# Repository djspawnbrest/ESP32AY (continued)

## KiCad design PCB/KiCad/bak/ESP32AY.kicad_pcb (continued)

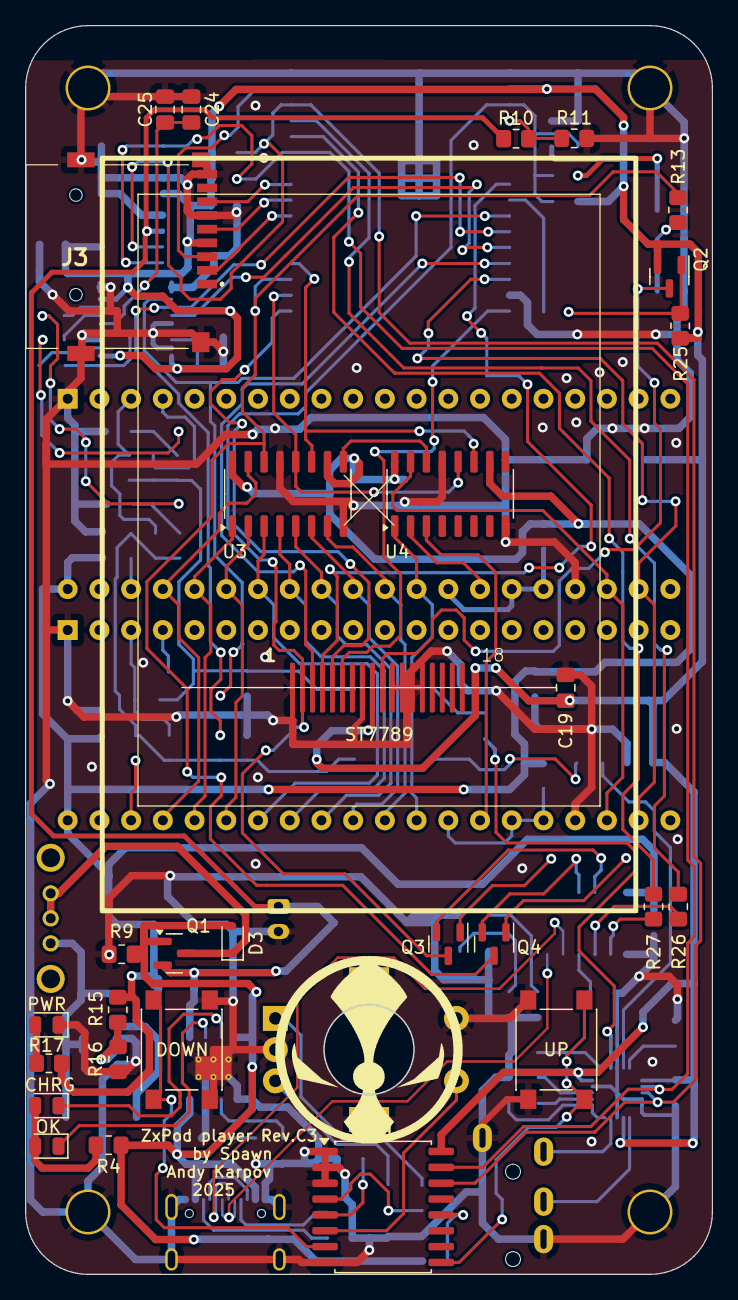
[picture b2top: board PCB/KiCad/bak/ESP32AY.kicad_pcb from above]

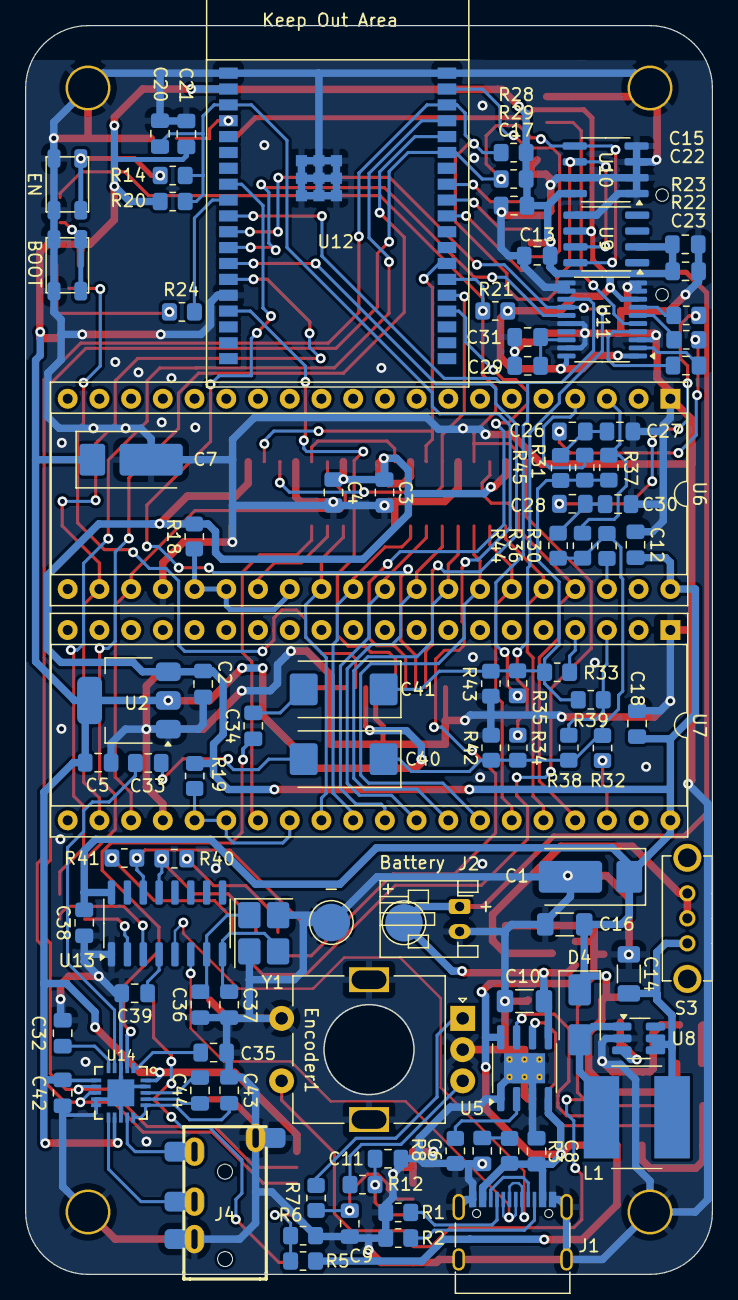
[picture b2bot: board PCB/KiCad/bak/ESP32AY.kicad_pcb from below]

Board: 2 copper layers, 55.0 x 100.0 mm, 127 parts (97 on the bottom side), 106 nets.

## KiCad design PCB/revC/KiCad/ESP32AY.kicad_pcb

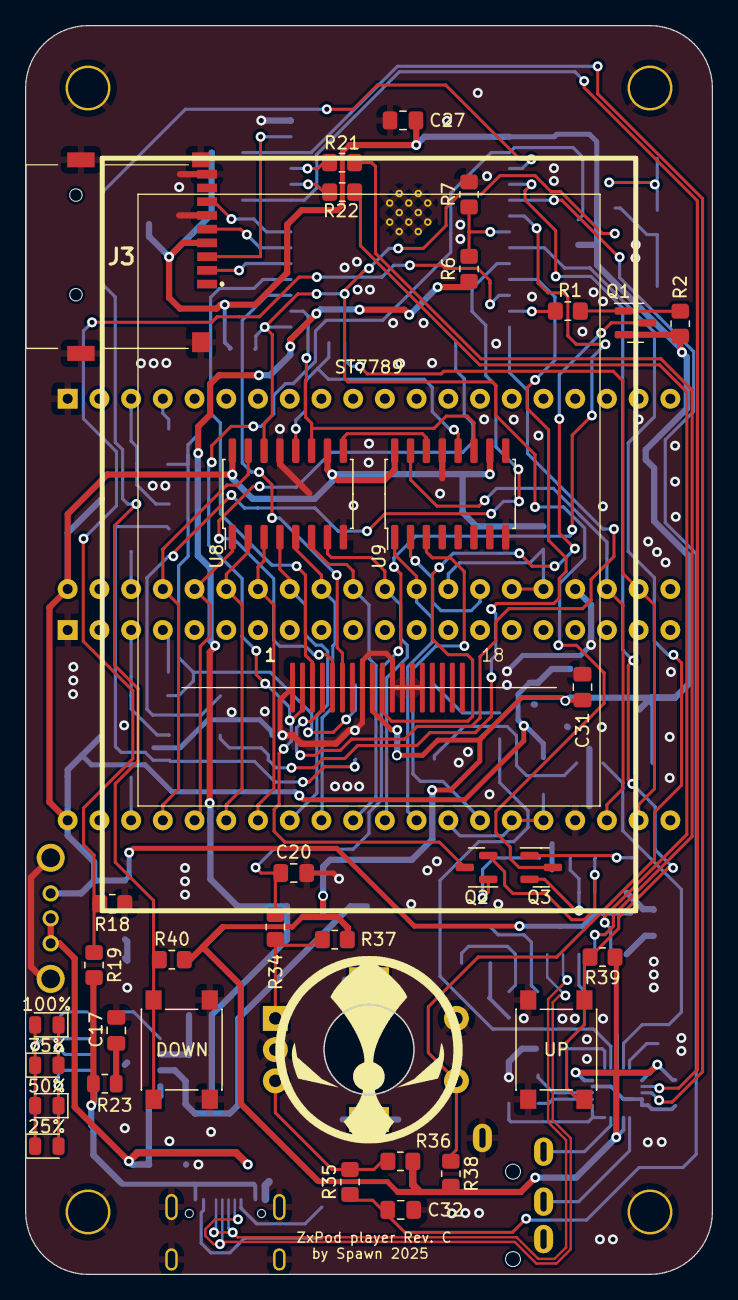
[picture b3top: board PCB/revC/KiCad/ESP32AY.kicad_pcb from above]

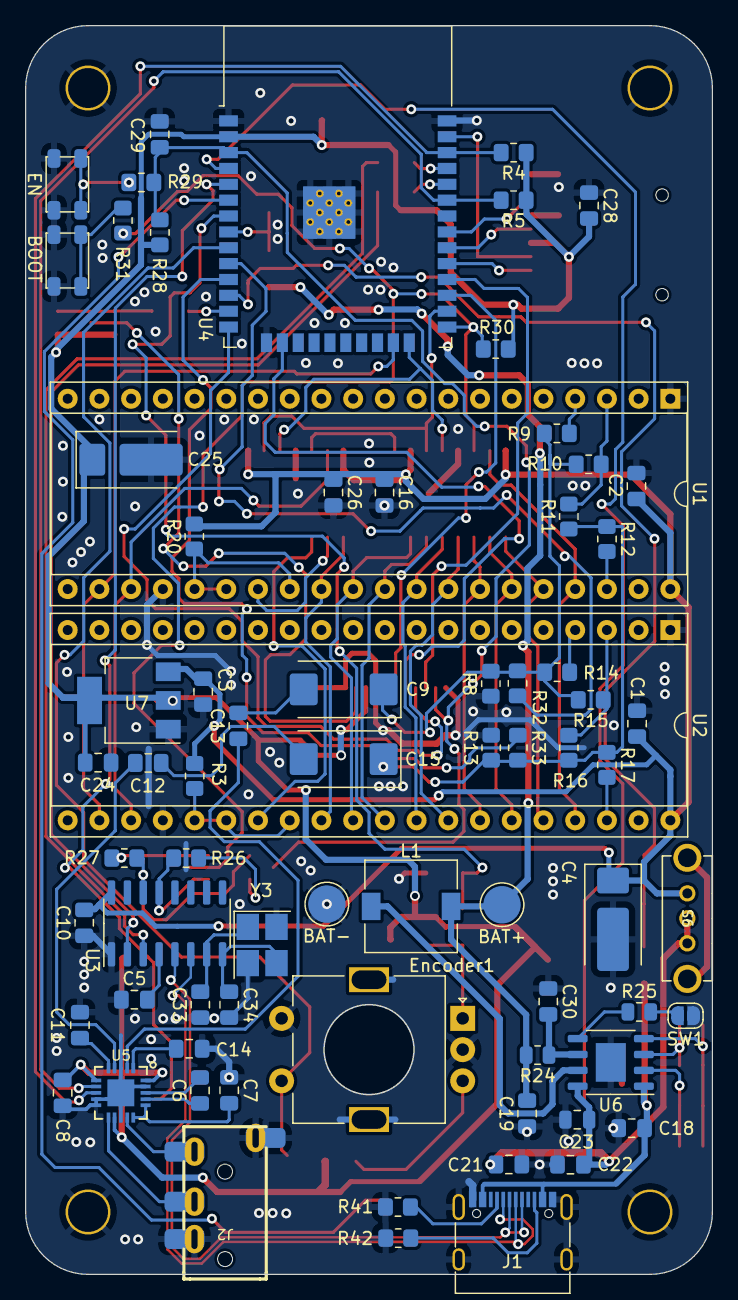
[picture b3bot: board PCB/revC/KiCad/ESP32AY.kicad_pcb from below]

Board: 2 copper layers, 55.0 x 100.0 mm, 107 parts (72 on the bottom side), 94 nets.

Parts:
BAT+1: BAT+; TestPoint_Pad_D3.0mm
BAT-1: BAT-; TestPoint_Pad_D3.0mm
C1, C2, C3, C5, C6, C7, C8, C10, C16, C20, C24, C26, C27, C28, C29, C31, C32: 100n; C_0805_2012Metric_Pad1.18x1.45mm_HandSolder
C4: 100uf; CP_EIA-7343-31_Kemet-D-uni
C9, C15: 100u; CP_EIA-7343-31_Kemet-D_Pad2.25x2.55mm_HandSolder
C11, C12, C13, C14: 470n; C_0805_2012Metric_Pad1.18x1.45mm_HandSolder
C17, C18: 10uf; C_0805_2012Metric_Pad1.18x1.45mm_HandSolder
C19, C21, C22, C30: 22uf; C_0805_2012Metric_Pad1.18x1.45mm_HandSolder
C23: 22uf; C_0805_2012Metric
C25: 47uf; CP_EIA-7343-31_Kemet-D-uni
C33, C34: 22p; C_0805_2012Metric_Pad1.18x1.45mm_HandSolder
D1: 25%; LED_0805_2012Metric
D2: 50%; LED_0805_2012Metric
D3: 75%; LED_0805_2012Metric
D4: 100%; LED_0805_2012Metric
Encoder1: RotaryEncoder_Switch; RotaryEncoder_Alps_EC11E-Switch_Vertical_H20mm
J1: USB_C_Receptacle_USB2.0_14P; USB_C_Receptacle_G-Switch_GT-USB-7010ASV
J2: MiniJack; AUDIO_JACK_3.5MM_SMD_TRRS_rounded_mixed
J3: SD Card; TFP09212B
L1: 1UH; L_7.3x7.3_H3.5
Q1: BC807; SOT-23
Q2, Q3: BC817; SOT-23
R1, R3, R20, R32, R33: 1K; R_0805_2012Metric_Pad1.20x1.40mm_HandSolder
R2, R7, R10, R11, R15, R16, R18, R26, R27, R28, R30, R34, R35, R36, R37, R38, R39, R40: 10K; R_0805_2012Metric_Pad1.20x1.40mm_HandSolder
R4, R5, R9, R12, R14, R17: 4.7K; R_0805_2012Metric_Pad1.20x1.40mm_HandSolder
R6: 100K; R_0805_2012Metric_Pad1.20x1.40mm_HandSolder
R8, R13: 510; R_0805_2012Metric_Pad1.20x1.40mm_HandSolder
R19: 8,2К*; R_0805_2012Metric_Pad1.20x1.40mm_HandSolder
R21, R22: 470; R_0805_2012Metric_Pad1.20x1.40mm_HandSolder
R23: 2R; R_0805_2012Metric
R24: 0.5R; R_0805_2012Metric
R25: 10K; R_0805_2012Metric
R29, R31: 220; R_0805_2012Metric_Pad1.20x1.40mm_HandSolder
R41, R42: 5K1; R_0805_2012Metric_Pad1.20x1.40mm_HandSolder
S2: DOWN; SW_Push_1P1T_NO_6x6mm_H9.5mm
S4: UP; SW_Push_1P1T_NO_6x6mm_H9.5mm
S6: EG1213; SW_EG1213
SW1: Check bat; SolderJumper-2_P1.3mm_Open_RoundedPad1.0x1.5mm
SW2: EN; SW_SPST_PTS810_handsoldering
SW3: BOOT; SW_SPST_PTS810_handsoldering
TFT1: ST7789
U1, U2: AY-3-8910; DIP-40_W15.24mm_Socket
U3: CH340G; SOIC-16_3.9x9.9mm_P1.27mm
U4: ESP32-WROOM-32
U5: TPA6130A2RTJTG4; QFN50P400X400X80-21N
U6: IP5306; HSOP-8-1EP_3.9x4.9mm_P1.27mm_EP2.41x3.1mm
U7: AMS1117-3.3; SOT-223-3_TabPin2
U8, U9: 74HC595; SO-16_5.3x10.2mm_P1.27mm
Y3: 12MHz; Crystal_SMD_3225-4Pin_3.2x2.5mm_HandSoldering

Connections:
595_CLOCK: U4.26 (IO4), U8.11 (SRCLK), U9.11 (SRCLK)
595_DATA: Q3.3 (C), R30.2, R31.1, U4.25 (IO0), U8.14 (SER)
595_LATCH: U4.24 (IO2), U8.12 (RCLK), U9.12 (RCLK)
+3.3V: C8.2, C24.1, C25.1, C27.1, C28.2, C31.2, J3.4 (VDD), Q1.2 (E), R2.2, R4.1, R5.1, R28.1, R30.1, R36.2, R37.1, R38.2, R39.1, R40.2, TFT1.9 (VCC), U4.2 (VDD), U5.6 (~SD), U5.12 (VDD_2), U5.20 (VDD), U7.2 (VO)
+5V: C1.2, C2.2, C3.1, C4.1, C10.2, C16.1, C26.1, R3.2, R20.2, S6.3, U1.40 (5V), U2.40 (5V), U3.16 (VCC), U7.3 (VI), U8.10 (~SRCLR), U8.16 (VCC), U9.10 (~SRCLR), U9.16 (VCC)
AY1_A: R9.2, U1.4 (CHANNEL_A)
AY1_A8: R20.1, U1.25 (A8), U1.26 (TEST2), U1.28 (BC2)
AY1_B: R10.1, R11.2, U1.3 (CHANNEL_B)
AY1_BDIR: U1.27 (BDIR), U9.2 (QC)
AY1_C: R12.2, U1.38 (CHANNEL_C)
AY2_A: R14.2, U2.4 (CHANNEL_A)
AY2_A8: R3.1, U2.25 (A8), U2.26 (TEST2), U2.28 (BC2)
AY2_B: R15.1, R16.2, U2.3 (CHANNEL_B)
AY2_BDIR: U2.27 (BDIR), U9.3 (QD)
AY2_C: R17.2, U2.38 (CHANNEL_C)
AYMIX_L: C9.1, R8.1, R9.1, R10.2, R14.1, R15.2, R32.1
AYMIX_R: C15.1, R11.1, R12.1, R13.1, R16.1, R17.1, R33.1
AY_BC1: U1.29 (BC1), U2.29 (BC1), U9.1 (QB)
AY_CLK: U1.22 (CLK), U2.22 (CLK), U4.23 (IO15)
AY_D0: U1.37 (DA0), U2.37 (DA0), U8.15 (QA)
AY_D1: U1.36 (DA1), U2.36 (DA1), U8.1 (QB)
AY_D2: U1.35 (DA2), U2.35 (DA2), U8.2 (QC)
AY_D3: U1.34 (DA3), U2.34 (DA3), U8.3 (QD)
AY_D4: U1.33 (DA4), U2.33 (DA4), U8.4 (QE)
AY_D5: U1.32 (DA5), U2.32 (DA5), U8.5 (QF)
AY_D6: U1.31 (DA6), U2.31 (DA6), U8.6 (QG)
AY_D7: U1.30 (DA7), U2.30 (DA7), U8.7 (QH)
AY_RST: U1.23 (/RESET), U2.23 (/RESET), U9.15 (QA)
BT_DN: R40.1, S2.3, S2.4, U4.4 (SENSOR_VP/IO36)
BT_UP: R39.2, S4.3, S4.4, U4.5 (SENSOR_VN/IO39)
Bat+: BAT+1.1, C19.2, L1.2, R6.1, R24.2
DAC_SOUND_L: R32.2, U4.10 (DAC1/IO25)
DAC_SOUND_R: R33.2, U4.11 (DAC2/IO26)
ENC_A: C20.1, R34.1, U4.7 (IO35)
ENC_B: C32.2, R35.1, U4.6 (IO34)
ENC_OK: Encoder1.S1, R38.1, U4.9 (IO33)
ESP_EN: C29.1, Q2.3 (C), R28.2, R29.1, TFT1.2 (RST), U4.3 (EN)
GND: BAT-1.1, C1.1, C2.1, C3.2, C4.2, C5.1, C7.1, C8.1, C10.1, C11.1, C14.2, C16.2, C17.1, C18.1, C19.1, C20.2, C21.2, C22.2, C23.2, C24.2, C25.2, C26.2, C27.2, C28.1, C29.2, C30.1, C31.1, C32.1, C33.1, C34.1, Encoder1.C, Encoder1.S2, J1.A1 (GND), J1.A12 (GND), J1.B1 (GND), J1.B12 (GND), J1.S1 (SHIELD), J2.R2, J2.S, J3.6 (VSS), J3.9 (CARD_DETECTION), J3.10 (GND), J3.11, J3.12, J3.13, R7.2, R8.2, R13.2, R18.1, R41.2, R42.2, S2.1, S2.2, S4.1, S4.2, SW1.1, SW2.1 (A), SW3.1 (A), TFT1.1 (GND), TFT1.8 (GND), TFT1.11 (LED1-), TFT1.12 (LED2-), TFT1.13 (LED3-), TFT1.14 (LED4-), U1.1 (GND), U1.24 (/A9), U2.1 (GND), U2.24 (/A9), U3.1 (GND), U4.1 (GND), U4.15 (GND), U4.38 (GND), U4.39 (GND), U5.3 (GND_2), U5.9 (GND_3), U5.10 (GND_4), U5.13 (GND_5), U5.19 (GND), U5.21 (EP), U6.9 (GND), U7.1 (GND), U8.8 (GND), U8.13 (~OE), U9.8 (GND), U9.13 (~OE), Y3.2, Y3.4
HP_L: J2.T, U5.14 (HPLEFT)
HP_R: J2.R1, U5.11 (HPRIGHT)
MIX_L: C9.2, C13.2
MIX_R: C12.2, C15.2
unnamed: C17.2, R23.2
unnamed: D1.2 (A), D2.1 (K), U6.2 (LED1)
unnamed: D1.1 (K), D2.2 (A), D3.1 (K), D4.2 (A), U6.4 (LED3)
unnamed: D3.2 (A), D4.1 (K), U6.3 (LED2)
unnamed: Encoder1.A, R34.2, R37.2
unnamed: Encoder1.B, R35.2, R36.1
unnamed: J1.A5 (CC1), R41.1
unnamed: J1.B5 (CC2), R42.1
unnamed: Q1.1 (B), R1.1, R2.1
unnamed: Q2.1 (B), R26.2
unnamed: Q2.2 (E), R27.1, U3.14 (~RTS)
unnamed: Q3.1 (B), R27.2
unnamed: Q3.2 (E), R26.1, U3.13 (~DTR)
unnamed: R25.2, SW1.2
unnamed: R29.2, SW2.2 (B)
unnamed: R31.2, SW3.2 (B)
unnamed: C5.2, U3.4 (V3)
unnamed: C33.2, U3.7 (XI), Y3.1
unnamed: C34.2, U3.8 (XO), Y3.3
unnamed: R22.2, U4.34 (RXD0/IO3)
unnamed: R21.2, U4.35 (TXD0/IO1)
unnamed: C6.1, U5.17 (CPN)
unnamed: C6.2, U5.18 (CPP)
unnamed: C7.2, U5.15 (CPVSS_2), U5.16 (CPVSS)
unnamed: C14.1, U5.1 (LEFTINM)
unnamed: C13.1, U5.2 (LEFTINP)
unnamed: C11.2, U5.5 (RIGHTINM)
unnamed: C12.1, U5.4 (RIGHTINP)
unnamed: C30.2, R24.1, U6.6 (BAT)
unnamed: R25.1, U6.5 (KEY)
unnamed: L1.1, U6.7 (SW)
unnamed: C21.1, C22.1, C23.1, S6.1, S6.2, U6.8 (Vout)
unnamed: U8.9 (QH'), U9.14 (SER)
RX0: R22.1, U3.2 (TXD)
SCL: R4.2, U4.36 (IO22), U5.8 (SCL)
SDA: R5.2, U4.33 (IO21), U5.7 (SDA)
SD_CS: J3.2 (CD/DAT3), U4.29 (IO5)
SPI_CLK: J3.5 (CLK), U4.30 (IO18)
SPI_MISO: J3.7 (DAT0), U4.31 (IO19)
SPI_MOSI: J3.3 (CMD), U4.37 (IO23)
TFT_CLK: TFT1.3 (SCK), U4.28 (IO17)
TFT_CS: TFT1.5 (CS), U4.16 (IO13)
TFT_DC: TFT1.4 (D/C), U4.14 (IO12)
TFT_LED: Q1.3 (C), TFT1.10 (LED+)
TFT_MOSI: TFT1.6 (SDA(MOSI)), U4.27 (IO16)
TFT_PWM: R1.2, U4.13 (IO14)
TX0: R21.1, U3.3 (RXD)
UD+: J1.A6 (D+), J1.B6 (D+), U3.5 (UD+)
UD-: J1.A7 (D-), J1.B7 (D-), U3.6 (UD-)
USB_SENS: R18.2, R19.1, U4.12 (IO27)
Vin: C18.2, J1.A4 (VBUS), J1.A9 (VBUS), J1.B4 (VBUS), J1.B9 (VBUS), R19.2, R23.1, U6.1 (Vin)
Vsens: R6.2, R7.1, U4.8 (IO32)

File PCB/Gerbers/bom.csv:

Designator,Footprint,Quantity,Value,LCSC Part #
"_4, _3, _2, ",,4,,
BAT+1,TestPoint_Pad_D3.0mm,1,BAT+,
BAT-1,TestPoint_Pad_D3.0mm,1,BAT-,
"C1, C10, C16, C2, C20, C24, C26, C27, C28, C29, C3, C31, C32, C5, C6, C7, C8",0805,17,100n,
"C11, C12, C13, C14",0805,4,470n,
"C15, C9",CP_EIA-7343-31_Kemet-D_Pad2.25x2.55mm_HandSolder,2,100u,
"C17, C18",0805,2,10uf,
"C19, C21, C22, C23",0805,4,22uf,
C25,CP_EIA-7343-31_Kemet-D-uni,1,47uf,
"C33, C34",0805,2,22,
C4,CP_EIA-7343-31_Kemet-D-uni,1,100uf,
D1,0805,1,25%,
D2,0805,1,50%,
D3,0805,1,75%,
D4,0805,1,100%,
ENCODER1,RotaryEncoder_Alps_EC11E-Switch_Vertical_H20mm,1,RotaryEncoder_Switch,
J1,USB_C_Receptacle_G-Switch_GT-USB-7010ASV,1,USB_C_Receptacle_USB2.0_14P,
J2,AUDIO_JACK_3.5MM_SMD_TRRS_rounded_mixed,1,MiniJack,
J3,TFP09212B,1,SD Card,
L1,L_7.3x7.3_H3.5,1,1UH,
Q1,SOT-23,1,BC807,
"Q2, Q3",SOT-23,2,BC817,
"R1, R20, R3, R32, R33",0805,5,1K,
"R10, R11, R15, R16, R18, R2, R25, R26, R27, R28, R30, R34, R35, R36, R37, R38, R39, R40",0805,18,10K,
"R12, R14, R17, R4, R5, R9",0805,6,4.7K,
"R13, R8",0805,2,510,
R19,0805,1,0,
"R21, R22",0805,2,470,
R23,0805,1,0.1R,
R24,0805,1,R50,
"R29, R31",0805,2,220,
"R41, R42",0805,2,5K1,
R6,0805,1,100K,
R7,0805,1,20K,
S2,SW_Push_1P1T_NO_6x6mm_H9.5mm,1,DOWN,
S4,SW_Push_1P1T_NO_6x6mm_H9.5mm,1,UP,
S6,SW_EG1213,1,EG1213,
SW1,SolderJumper-2_P1.3mm_Open_RoundedPad1.0x1.5mm,1,SW_Push,
SW2,SW_SPST_PTS810_handsoldering,1,EN,
SW3,SW_SPST_PTS810_handsoldering,1,BOOT,
TFT1,ST7789,1,ST7789,
"U1, U2",DIP-40_W15.24mm_Socket,2,AY-3-8910,
U3,SOIC-16_3.9x9.9mm_P1.27mm,1,CH340G,
U4,ESP32-WROOM-32,1,ESP32-WROOM-32,
U5,QFN50P400X400X80-21N,1,TPA6130A2RTJTG4,TPA6130A2RTJTG4
U6,HSOP-8-1EP_3.9x4.9mm_P1.27mm_EP2.41x3.1mm,1,SM5308,
U7,SOT-223-3_TabPin2,1,AMS1117-3.3,
"U8, U9",SO-16_5.3x10.2mm_P1.27mm,2,74HC595,
Y3,Crystal_SMD_3225-4Pin_3.2x2.5mm_HandSoldering,1,12MHz,

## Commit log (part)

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2024-06-26 first
2024-06-26 some cleans
2024-06-26 add PCB project and Gerbers
2024-06-26 add Case stl models
2024-10-02 fix build and upload littlefs
2024-10-02 fix noise on dac
2024-10-03 add builded firmwares
2024-10-03 fix build littlefs image
2024-10-04 Added fast flash firmware feature
2024-10-06 udate encButton library
2024-10-06 upate version build
2024-10-22 add: new feature - Playing over UART
2024-10-22 update: firmware with v3.2
2024-10-22 fix: settings menu bug
2024-11-13 PCB Rev. B (Type-C and Stereo DAC)
2024-11-20 fix backlight screen noise
2024-11-20 Dual Channel DAC for PCB rev.B
2025-02-09 fix issues #5 and #6, add search supported files on whole SD card includes subfolders.
2025-02-09 fix: firmware version
2025-02-09 fix: highlight the playback folder in the file browser along the entire path.
2025-02-09 fix: highlight whole playing path path folders and playlists
2025-02-16 fix: some errors with spi class and backlight setup
2025-03-04 Release 3.4 (added mod+s3m formats), LCD moved to dedicated SPI with revision C PCB or soldering upgrade from revision A and B to revision C (see README). Some optimizations and new features.
2025-04-09 Refactored schematics, updated BOM
2025-04-09 Updated page settings (revision number, etc)
2025-04-10 Added C30 to the charger unit
2025-04-10 Fixed R7 from 20k to 10k
2025-04-11 Fix extit from config menu (volume triggered on exit), fix silence on pause and change track, some changes on "about" screen:)
2025-04-14 Add root config for change encoder type (see README) and reset config before start up.
2025-04-14 add release button notification on enter root menu
2025-04-14 fix mod jump order loop song on last order
2025-04-14 Diff from Spawn with 2 configs - on sd card and littlefs
2025-04-14 Schematics change: replaced R19 from 0 to 8K2
2025-04-16 remove debug notifications from separate configs load/save
2025-04-16 add support for external DAC's
2025-04-16 add file remove feature
2025-04-16 Update firmwares bin
2025-04-29 RevC1 - initial commit
2025-04-29 Rev.C1 - initial PCM5102A DAC support
2025-04-29 Updated rev.C1 - added JST-PH connector
2025-05-10 Rev.C2 initial revision
2025-05-21 add encoder direction setting in config menu
2025-05-23 fix encoder direction start initialization
2025-05-28 initial C3 schematic, pcb, code.
2025-05-28 add gerbers and ibom
2025-06-15 fix: battery calibration actions in menu
2025-06-16 Add RTC and EEPROM features, prepare to rev. D PCB (ESP32S3)
2025-06-16 fix short day of week on main screen instead of long
2025-06-16 fix bin file for ESP32S3
2025-06-18 organizing all PCB revisions into their own folders
2025-06-18 fix rtc debug
2025-06-19 add mod samples in PSRAM on S3. fix some actions in channelEQ in mods.
2025-06-19 fix EQ channel buffer for s3m when more 8 channels
2025-06-21 fix s3m 16-bit samples and skip OPL samples.
2025-06-21 add s3m PSRAM support for ESP32-S3 with PSRAM. Some s3m fixes.
2025-06-21 fix some spaces in code.
2025-06-21 fix gitignore
2025-06-21 init xm implementation
2025-07-14 fix amp and rtc addresses
2025-07-16 added SD forwarding via USB as Mass Storage device (rev.D only)
2025-07-16 fix encoder default direction for rev.D
2025-07-16 Some minor fixes
2025-07-16 fix slow RTC setup
2025-07-30 Some PCB and code fixes
2025-09-12 Release 3.5 (added xm format). Some optimizations and new features.
2025-09-18 fix xm playing time calculation. add reset last playing track. minor fixes.
2025-10-09 fix ay format rendering and playing
2025-10-09 add support PT3.7+ TS with one module instead integrated two!
2025-10-09 fix ay BCA layer
2025-10-10 fix some issues when switching from the .ay format, add DAC Gain in config.
2025-10-10 add EQ for the beeper part in .ay format.
2025-10-15 Release 3.6 (added tap and tzx formats). Some optimizations and new features.
2025-10-15 fix pause on change tapes formats
2025-10-15 fix pause on change tapes formats and mass storage mount for rev.D
2025-10-15 fix time recalculating on change tapes turbo modes
2025-10-15 fix tape format levels, time recalculating after change turbo modes.
2025-10-17 fix TAPE formats with block change and turbo load modes + minor fixes.
2025-10-20 fix .mod patternloop effect, also check sample boundaries before processing the loop.
2025-10-20 fix .mod format - pattern loop effect with jump to 1 row instead of 0 row.
2025-11-07 add new cases
2025-11-08 Add .mp3 and wav formats
2025-11-09 some minor fixes + fix skip mp3 cover art in player.
2025-11-09 update fw bin files
2025-11-09 fix EQ mp3/wav mono bug.
2025-11-10 Many optimizations for RAM and screen rendering have been made, and file sorting has been added to the browser. some minor fixes.
2025-11-10 fix change ay clock on mp3/wav formats.
2025-11-10 update S3 bin file. also fix build bin script for new version.
2025-11-10 update postScripts and fw bin files.
2026-05-15 fix reset RTC, some minor fixes
2026-05-15 fix DAC formats volumes
2026-05-15 fix XM freezes, responsiveness of the encoder and buttons
2026-05-15 fix s3m volume balance on internal DAC
2026-05-15 implementation of the assembly number and date into the project
2026-05-16 fix player freeze on xm track change
2026-05-16 PSRAM leak fix
2026-05-16 switching from debug to production mode
2026-05-16 fix XM file validations and playback time
2026-05-17 fix .mod time calculation like OpenMPT, some minor fixes
2026-05-17 fix mod current time sync
2026-05-17 Fix MOD player: uint32_t for sample length and bounds checks
2026-05-17 Add rawPeriod field to support notes beyond standard period table
2026-05-17 Fixed closing notifications
2026-05-17 minor fix
2026-05-17 platformio.ini minor fix
2026-05-17 minor gain fix
2026-05-21 PSRAM leak fixed
2026-05-21 change platform to 7.0.1, add scrollbar in browser, add fast turn encoder in browser
2026-05-28 refactor SD-USB mount in CtartupConfig menu! (press left button and turn on player)
2026-05-30 fix SD<--->USB detect and mount
2026-05-31 changing USB descriptor names depending on the mode
2026-06-07 add revD2 where fix Audio mixer
2026-06-07 fix ay track change silence from playlists
